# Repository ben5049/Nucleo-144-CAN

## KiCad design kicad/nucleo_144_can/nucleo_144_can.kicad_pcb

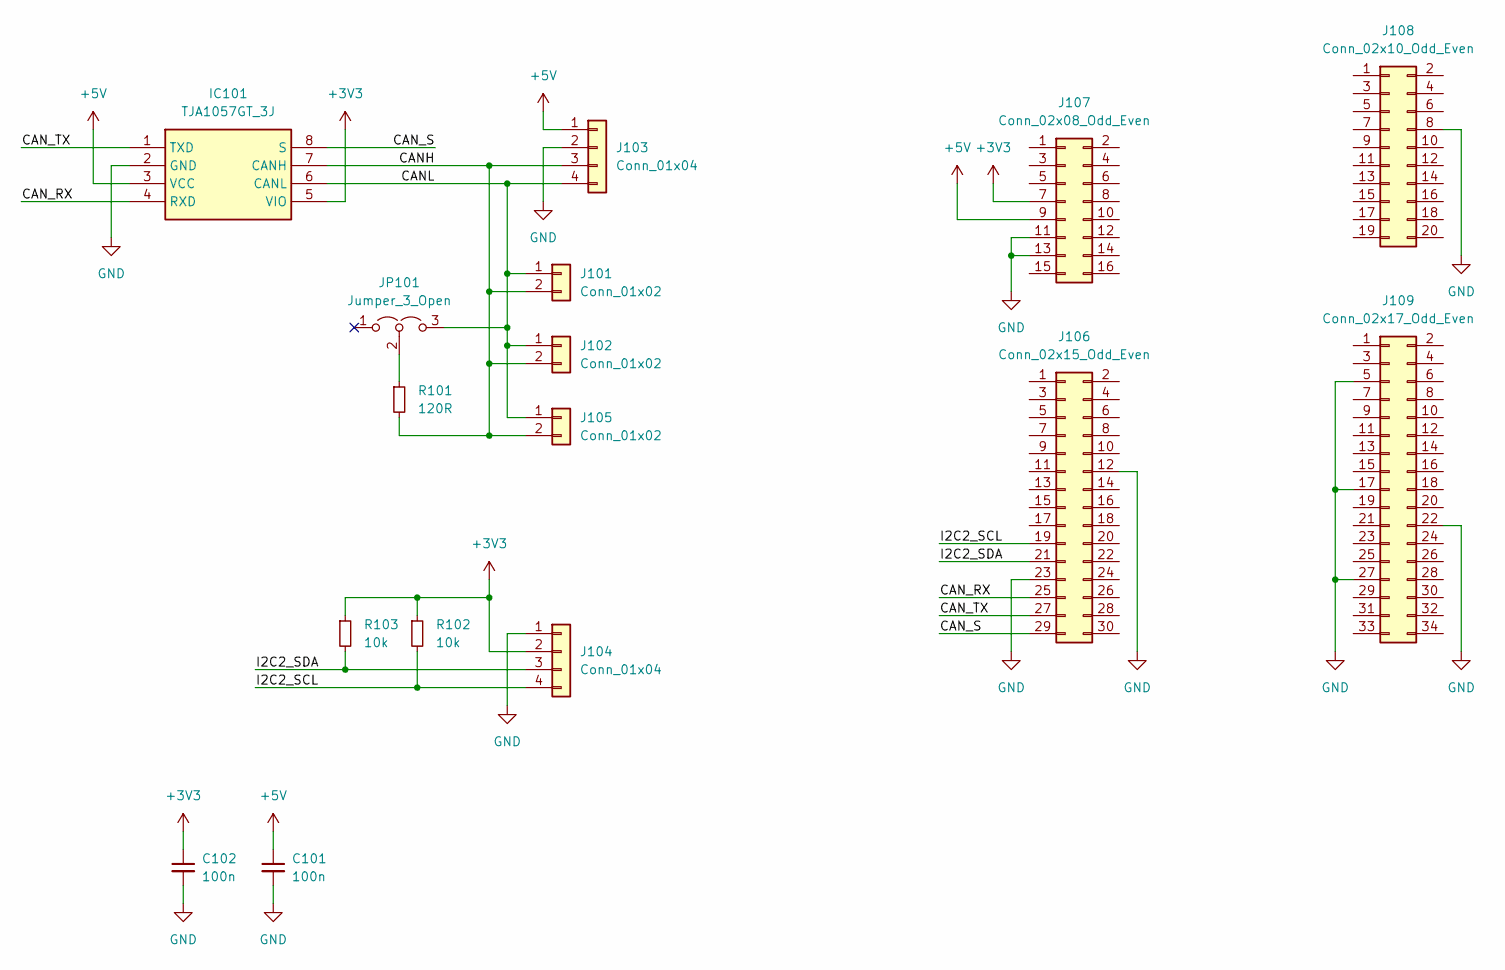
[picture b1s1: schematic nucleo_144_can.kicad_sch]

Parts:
C101, C102: 100n; C_0402_1005Metric
IC101: TJA1057GT_3J; SOIC127P600X175-8N; Manufacturer_Part_Number TJA1057GT/3J; Mouser Part Number 771-TJA1057GT/3J
J101, J102: Conn_01x02; JST_GH_SM02B-GHS-TB_1x02-1MP_P1.25mm_Horizontal
J103: Conn_01x04; JST_GH_SM04B-GHS-TB_1x04-1MP_P1.25mm_Horizontal
J104: Conn_01x04; JST_SH_SM04B-SRSS-TB_1x04-1MP_P1.00mm_Horizontal
J105: Conn_01x02; Samtec_HPM-02-05-x-S_Straight_1x02_Pitch5.08mm
J106: Conn_02x15_Odd_Even; PinHeader_2x15_P2.54mm_Vertical
J107: Conn_02x08_Odd_Even; PinHeader_2x08_P2.54mm_Vertical
J108: Conn_02x10_Odd_Even; PinHeader_2x10_P2.54mm_Vertical
J109: Conn_02x17_Odd_Even; PinHeader_2x17_P2.54mm_Vertical
JP101: Jumper_3_Open; PinHeader_1x03_P2.54mm_Vertical
R101: 120R; R_0402_1005Metric
R102, R103: 10k; R_0402_1005Metric

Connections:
+3V3: C102.1, IC101.5 (VIO), J104.2, J107.7, R102.1, R103.1
+5V: C101.1, IC101.3 (VCC), J103.1, J107.9
/CANH: IC101.7 (CANH), J101.2, J102.2, J103.3, J105.2, R101.2
/CANL: IC101.6 (CANL), J101.1, J102.1, J103.4, J105.1, JP101.3 (B)
/CAN_RX: IC101.4 (RXD), J106.25
/CAN_S: IC101.8 (S), J106.29
/CAN_TX: IC101.1 (TXD), J106.27
/I2C2_SCL: J104.4, J106.19, R102.2
/I2C2_SDA: J104.3, J106.21, R103.2
GND: C101.2, C102.2, IC101.2 (GND), J103.2, J104.1, J106.12, J106.23, J107.11, J107.13, J108.8, J109.5, J109.17, J109.22, J109.27
unnamed: JP101.2 (C), R101.1

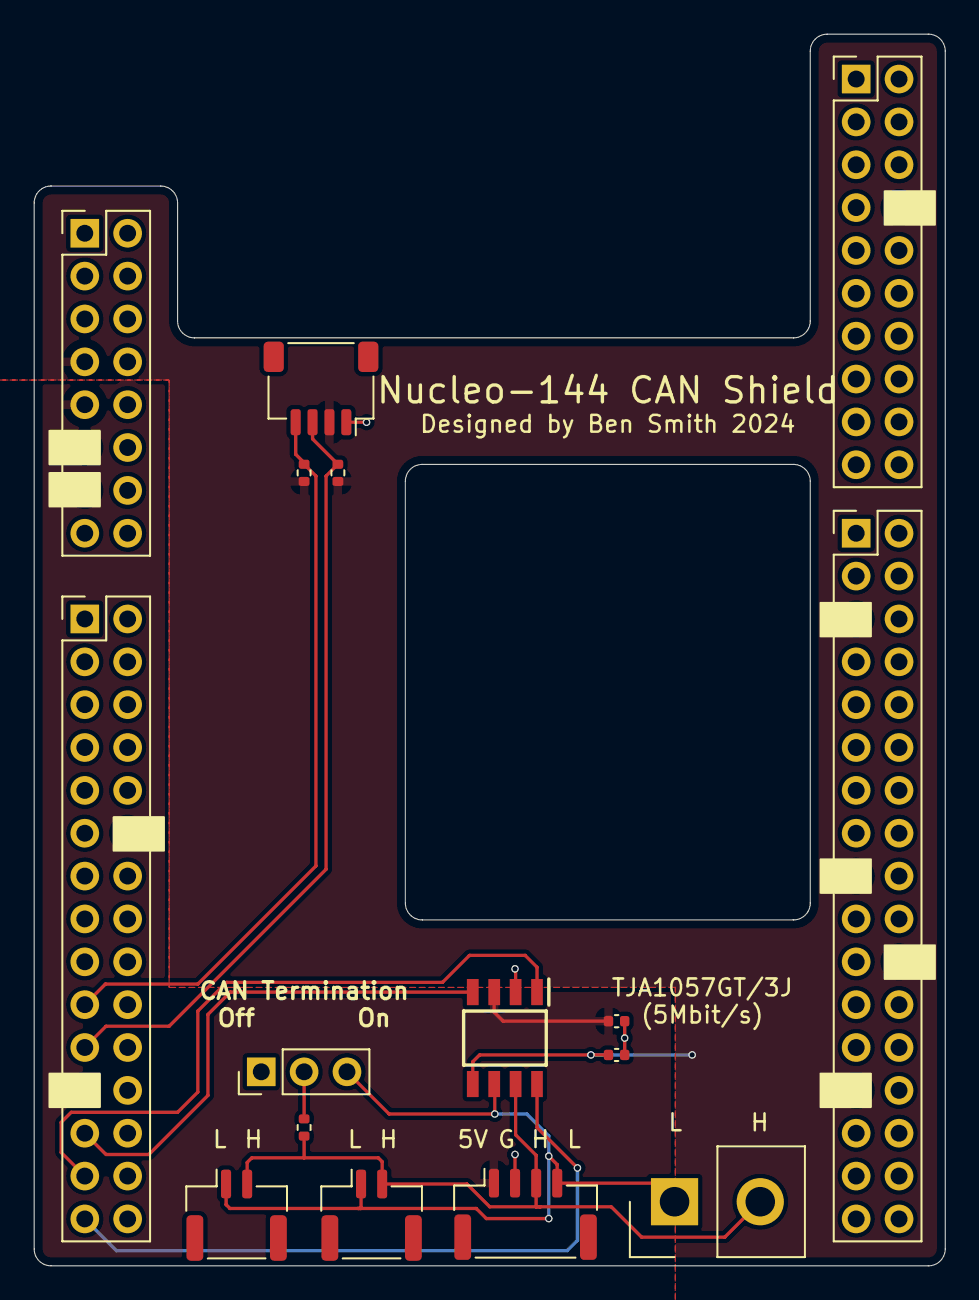
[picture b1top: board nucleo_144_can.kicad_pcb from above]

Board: 2 copper layers, 54.0 x 73.0 mm, 16 parts (0 on the bottom side), 11 nets.

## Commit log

2024-09-15 Board done
2024-09-15 Removed unecessary files
